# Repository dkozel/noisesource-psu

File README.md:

This is a computer controlled, portable power supply for RF Noise Sources such as the Keysight or Noisecom 346 series devices. It is powered by USB 2.0 and controlled without installing drivers from Linux, Windows, and OSX.

## Basic specs

Output:
* 28V +- 1V
* 100mA peak, 30-60mA average
* On/Off switching up to 1 Hz
* BNC female connector

Input:
* USB 2.0 compliant host
* 4.75 to 5.25 V
* 100 mA initial, 500 mA negotiated, 2.5 mA suspended
* USB 2.0 micro socket

Features:
* Output on/off control via USB command
* Optionally a switch to manually control output state
* LED showing output state
* LED showing input power good

## Software

The pyFTDI Python library allows the GPIO lines of an FT230X to be controlled from Linux, macOS, and Windows without the user installing any driver.

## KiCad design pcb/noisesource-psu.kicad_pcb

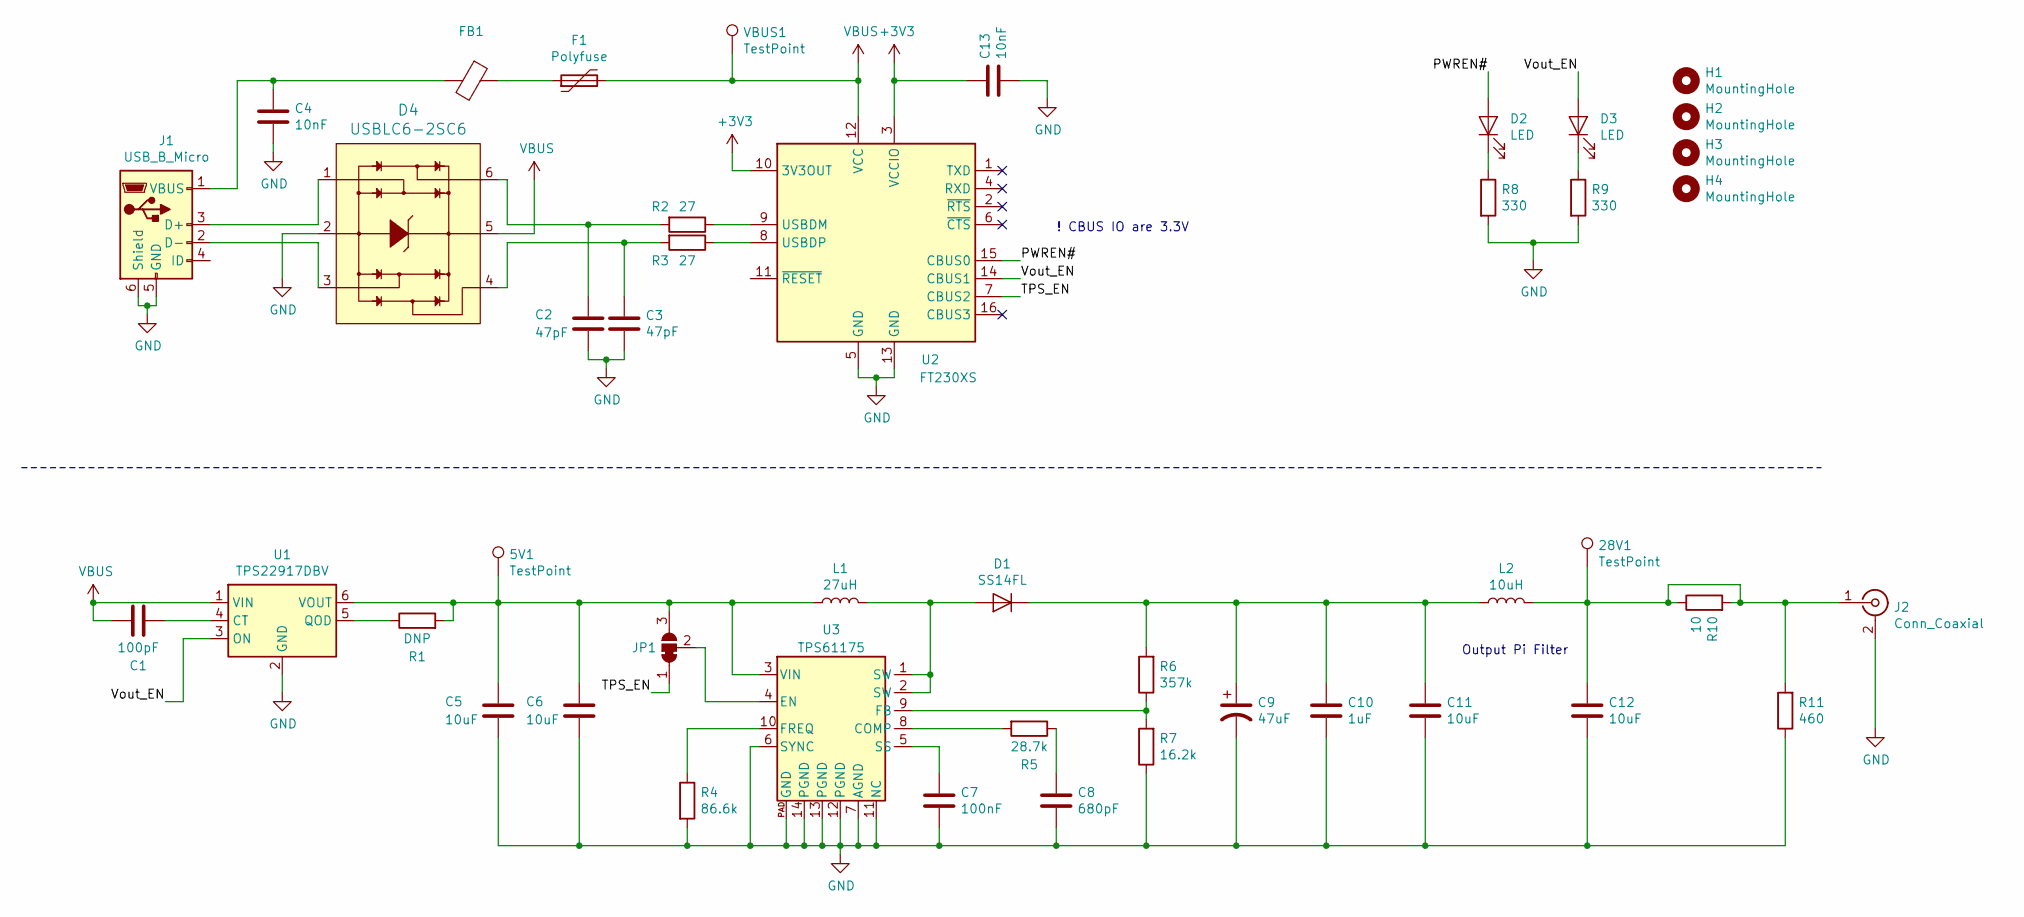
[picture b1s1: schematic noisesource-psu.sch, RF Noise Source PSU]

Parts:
5V1, 28V1: TestPoint; TestPoint_THTPad_1.0x1.0mm_Drill0.5mm
C1: 100pF; C_0603_1608Metric_Pad1.05x0.95mm_HandSolder; MPN 885012206003; Digi-Key PN 732-7922-1-ND
C2, C3: 47pF; C_0603_1608Metric_Pad1.05x0.95mm_HandSolder; MPN 885012006021; Digi-Key PN 732-7764-1-ND
C4, C13: 10nF; C_0603_1608Metric_Pad1.05x0.95mm_HandSolder; MPN 885012206040; Digi-Key PN 732-7959-1-ND
C5, C6, C11, C12: 10uF; C_0603_1608Metric_Pad1.05x0.95mm_HandSolder; MPN GRM188R6YA106MA73D; Digi-Key PN 490-13248-1-ND
C7: 100nF; C_0603_1608Metric_Pad1.05x0.95mm_HandSolder; MPN CL10B104KB8NFNC; Digi-Key PN 1276-1934-1-ND
C8: 680pF; C_0603_1608Metric_Pad1.05x0.95mm_HandSolder; MPN 885012206082; Digi-Key PN 732-8000-1-ND
C9: 47uF; C_Elec_8x6.2; MPN UUR1V470MCL6GS; Digi-Key PN 493-9586-1-ND
C10: 1uF; C_0603_1608Metric_Pad1.05x0.95mm_HandSolder; MPN UMK107BJ105KA-T; Digi-Key PN 587-2400-1-ND
D1: SS14FL; D_SOD-123F; MPN SS14FL; Digi-Key PN SS14FLCT-ND
D2, D3: LED; R_0603_1608Metric_Pad1.05x0.95mm_HandSolder; MPN 150060VS75000; Digi-Key PN 732-4980-1-ND
D4: USBLC6-2SC6; SOT23-6L; MPN USBLC6-2SC6; Digi-Key PN 497-5235-1-ND
F1: Polyfuse; Fuse_0805_2012Metric_Pad1.15x1.40mm_HandSolder; MPN 0805L110WR; Digi-Key PN F6725CT-ND
FB1: Ferrite_Bead; R_0603_1608Metric_Pad1.05x0.95mm_HandSolder; MPN BK1608HS220-T; Digi-Key PN 587-1869-1-ND
H1, H2, H3, H4: MountingHole; MountingHole_3.2mm_M3_Pad_Via
J1: USB_B_Micro; USB_Micro-AB_Molex_47590-0001; MPN 0475900001; Digi-Key PN WM17144CT-ND
J2: Conn_Coaxial; BNC_Amphenol_B6252HB-NPP3G-50_Horizontal; MPN B6252HB-NPP3G-50
JP1: SolderJumper_3_Bridged12; SolderJumper-3_P1.3mm_Bridged12_RoundedPad1.0x1.5mm
L1: 27uH; L_Bourns-SRN5040; MPN SRN5040-270M; Digi-Key PN SRN5040-270MCT-ND
L2: 10uH; L_Bourns-SRN5040; MPN SRN5040-100M; Digi-Key PN SRN5040-100MCT-ND
R1: DNP; R_0603_1608Metric_Pad1.05x0.95mm_HandSolder
R2, R3: 27; R_0603_1608Metric_Pad1.05x0.95mm_HandSolder; MPN RK73B1JTTD270J; Digi-Key PN 2019-RK73B1JTTD270JCT-ND
R4: 86.6k; R_0603_1608Metric_Pad1.05x0.95mm_HandSolder; MPN RK73H1JTTD8662F; Digi-Key PN 2019-RK73H1JTTD8662FCT-ND
R5: 28.7k; R_0603_1608Metric_Pad1.05x0.95mm_HandSolder; MPN RK73H1JTTD2872F; Digi-Key PN 2019-RK73H1JTTD2872FCT-ND
R6: 357k; R_0603_1608Metric_Pad1.05x0.95mm_HandSolder; MPN RK73H1JTTD3573F; Digi-Key PN 2019-RK73H1JTTD3573FCT-ND
R7: 16.2k; R_0603_1608Metric_Pad1.05x0.95mm_HandSolder; MPN RK73H1JTTD1622F; Digi-Key PN 2019-RK73H1JTTD1622FCT-ND
R8, R9: 330; R_0603_1608Metric_Pad1.05x0.95mm_HandSolder; MPN RK73B1JTTD331J; Digi-Key PN 2019-RK73B1JTTD331JCT-ND
R10: 10; R_0402_1005Metric; MPN 3502470RJT; Digi-Key PN A143324CT-ND
R11: 460; R_2010_5025Metric_Pad1.52x2.65mm_HandSolder; MPN 3502470RJT; Digi-Key PN A143324CT-ND
U1: TPS22917DBV; SOT-23-6; MPN TPS22917DBVR; Digi-Key PN 296-50498-1-ND
U2: FT230XS; SSOP-16_3.9x4.9mm_P0.635mm; MPN FT230XS-R; Digi-Key PN 768-1135-1-ND
U3: TPS61175; TSSOP14; MPN TPS61175PWPR; Digi-Key PN 296-24013-1-ND
VBUS1: TestPoint; TestPoint_THTPad_1.0x1.0mm_Drill0.5mm

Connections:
+3V3: C13.1, U2.3 (VCCIO), U2.10 (3V3OUT)
/PWREN#: D2.2 (A), U2.15 (CBUS0)
/TPS_EN: JP1.1 (A), U2.7 (CBUS2)
/Vout_EN: D3.2 (A), U1.3 (ON), U2.14 (CBUS1)
GND: C2.2, C3.2, C4.2, C5.1, C6.2, C7.2, C8.2, C9.2, C10.2, C11.2, C12.2, C13.2, D4.2, H1.1, H2.1, H3.1, H4.1, J1.5 (GND), J1.6 (Shield), J2.2 (Ext), R4.2, R7.1, R8.2, R9.2, R11.1, U1.2 (GND), U2.5 (GND), U2.13 (GND), U3.6 (SYNC), U3.7 (AGND), U3.11 (NC), U3.12 (PGND), U3.13 (PGND), U3.14 (PGND), U3.PAD (GND)
unnamed: 5V1.1, C5.2, C6.1, JP1.3 (B), L1.1, R1.2, U1.6 (VOUT), U3.3 (VIN)
unnamed: 28V1.1, C12.1, J2.1 (In), L2.2, R10.1, R10.2, R11.2
unnamed: C1.1, U1.4 (CT)
unnamed: C2.1, D4.6, R2.2
unnamed: C3.1, D4.4, R3.2
unnamed: C4.1, FB1.2, J1.1 (VBUS)
unnamed: C7.1, U3.5 (SS)
unnamed: C8.1, R5.1
unnamed: C9.1, C10.1, C11.1, D1.1 (K), L2.1, R6.2
unnamed: D1.2 (A), L1.2, U3.1 (SW), U3.2 (SW)
unnamed: D2.1 (K), R8.1
unnamed: D3.1 (K), R9.1
unnamed: D4.1, J1.3 (D+)
unnamed: D4.3, J1.2 (D-)
unnamed: F1.1, FB1.1
unnamed: JP1.2 (C), U3.4 (EN)
unnamed: R1.1, U1.5 (QOD)
unnamed: R2.1, U2.9 (USBDM)
unnamed: R3.1, U2.8 (USBDP)
unnamed: R4.1, U3.10 (FREQ)
unnamed: R5.2, U3.8 (COMP)
unnamed: R6.1, R7.2, U3.9 (FB)
VBUS: C1.2, D4.5, F1.2, U1.1 (VIN), U2.12 (VCC), VBUS1.1

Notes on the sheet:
! CBUS IO are 3.3V
Output Pi Filter

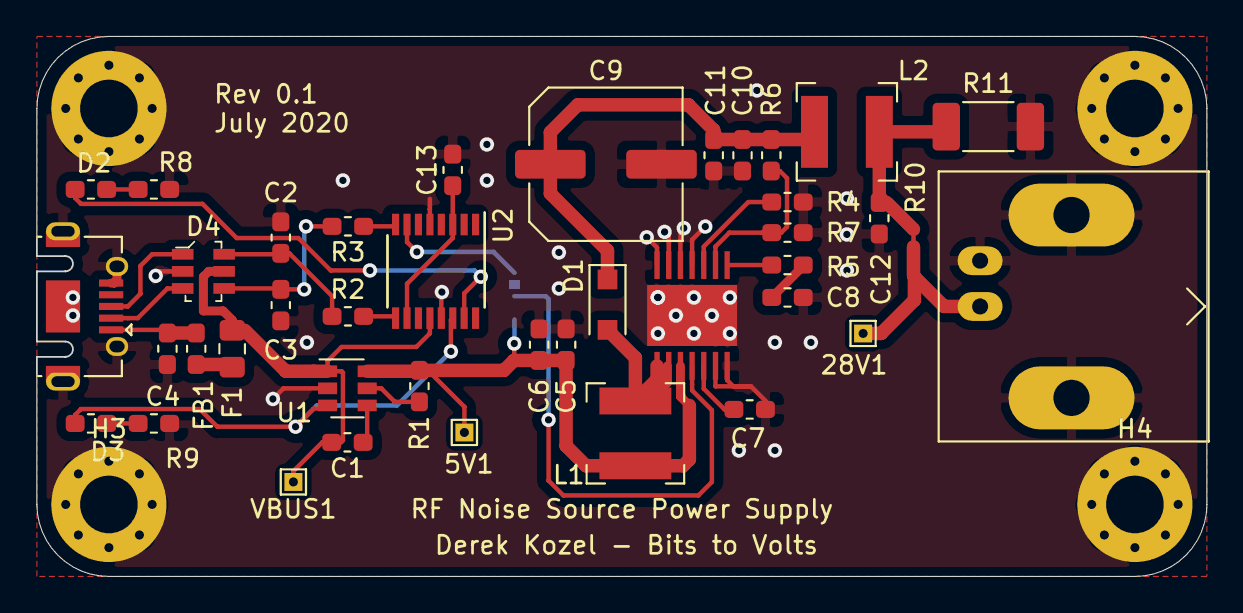
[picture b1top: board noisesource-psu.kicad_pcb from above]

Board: 2 copper layers, 65.0 x 30.0 mm, 45 parts (1 on the bottom side), 28 nets.

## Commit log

2020-04-14 Initial project creation
2020-04-14 git: Added fp-info-cache to gitignore
2020-04-14 docs: Added initial project description
2020-04-14 pcb: Continued initial schematic creation
2020-04-17 pcb: Added TPS61175 symbol to project library
2020-04-17 pcb: Changed voltage regulator to TPS61175
    The previous TLV61046 is not rated to handle the peak inductor
    currents during startup.
2020-06-15 Updated schematic
    Added PDF export
    Added comments on output filter and output switch
2020-07-07 schematic: Added output filter, added footprints
2020-07-08 pcb: Updated schematic and layout
    Schematic:
    Added testpoints
    Added ground pad to TPS51175
    Layout:
    Completed initial layout of PCB
2020-07-09 pcb: Updated schematic and layout
    Added 3.3v decoupling cap
    Added top ground fill
    Changed solder jumper footprint
    Added sense and test load resistors
    Changed SMPS ground pad to thermal fill
    Changed mounting holes to plated through vias with pads
